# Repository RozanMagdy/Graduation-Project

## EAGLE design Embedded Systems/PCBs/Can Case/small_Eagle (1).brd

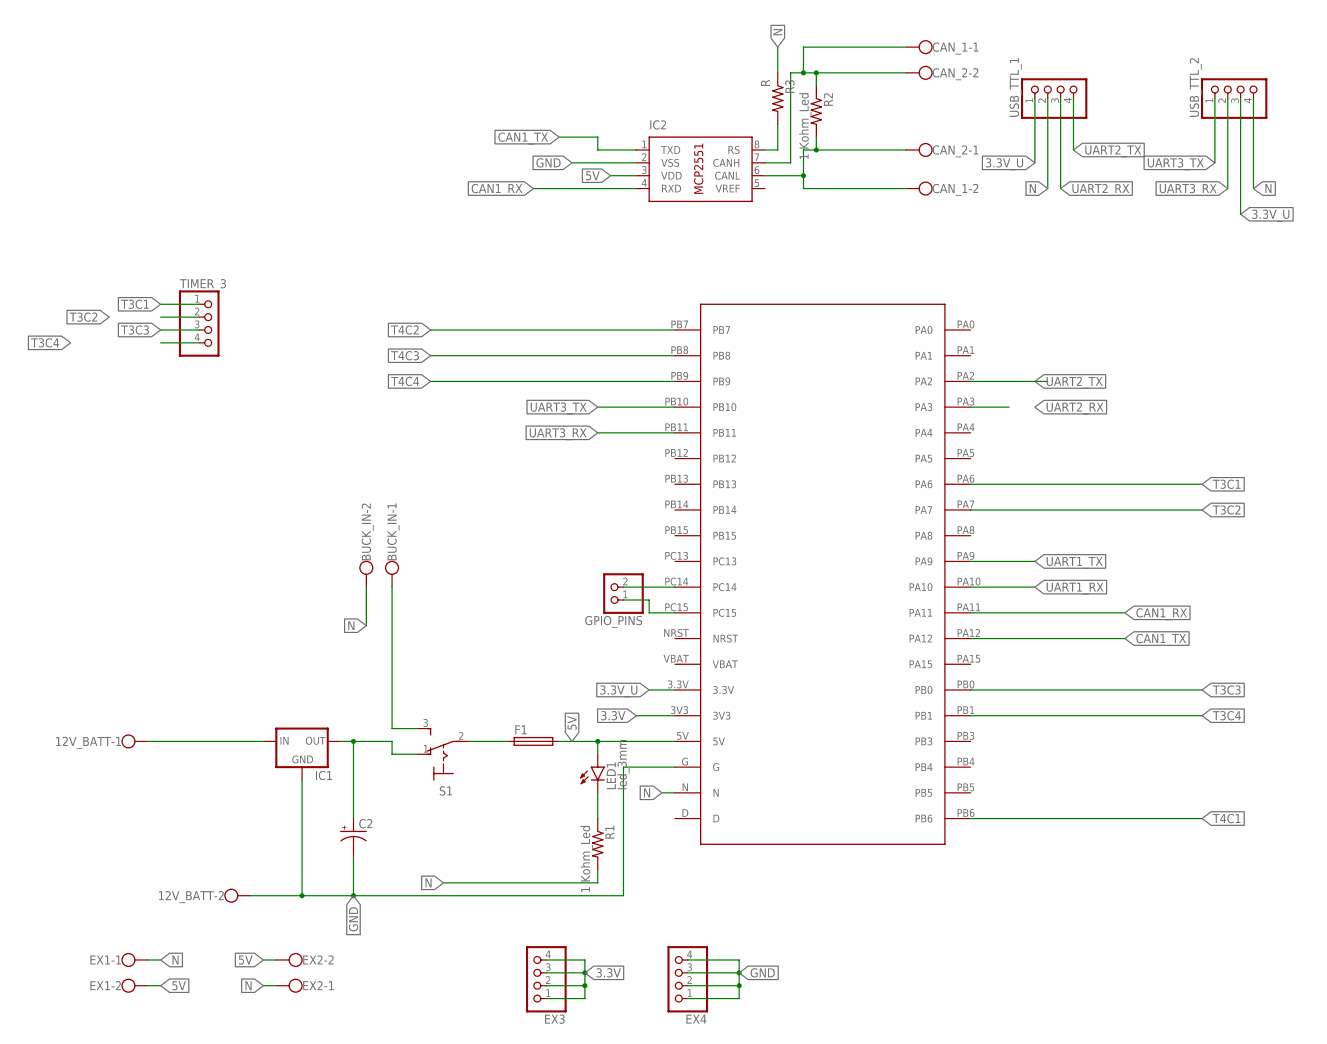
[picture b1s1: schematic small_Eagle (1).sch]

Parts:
12V_BATT: W237-102
BUCK_IN: W237-102
C2: CPOL-USE2-4; E2-4
CAN_1, CAN_2: W237-102
EX1, EX2: W237-102
EX3, EX4: PINHD-1X4; 1X04
F1: GSH15
GPIO_PINS: PINHD-1X2; 1X02
IC1: 78XXS
IC2: MCP2551/P; DIL08
LED1: led_3mm; LED3MM
R1, R2: 1 Kohm_Led; 0207/7
R3: R; 0207/7
S1: 320-916
TIMER_3: PINHD-1X4; 1X04
U$1: STM32F103C8; DIP
USB_TTL_1, USB_TTL_2: PINHD-1X4; 1X04

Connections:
3.3V: EX3.1, EX3.2, EX3.3, EX3.4, U$1.3V3
3.3V_U: U$1.3.3V, USB_TTL_1.1, USB_TTL_2.3
5V: EX1.2, EX2.2, F1.2, IC2.3 (VDD), LED1.A, U$1.5V
CAN1_RX: IC2.4 (RXD), U$1.PA11
CAN1_TX: IC2.1 (TXD), U$1.PA12
GND: 12V_BATT.2, C2.-, EX4.1, EX4.2, EX4.3, EX4.4, IC1.GND, IC2.2 (VSS), U$1.G
GPIO_PINS: GPIO_PINS.1, U$1.PC15
N: BUCK_IN.2, EX1.1, EX2.1, R1.2, R3.1, U$1.N, USB_TTL_1.2, USB_TTL_2.4
unnamed: BUCK_IN.1, S1.3 (S)
unnamed: CAN_1.2, CAN_2.1, IC2.6 (CANL), R2.2
unnamed: LED1.K (C), R1.1
unnamed: F1.1, S1.2
unnamed: 12V_BATT.1, IC1.IN
unnamed: C2.+, IC1.OUT, S1.1 (O)
unnamed: IC2.8 (RS), R3.2
unnamed: GPIO_PINS.2, U$1.PC14
unnamed: CAN_1.1, CAN_2.2, IC2.7 (CANH), R2.1
T3C1: TIMER_3.1, U$1.PA6
T3C2: TIMER_3.2, U$1.PA7
T3C3: TIMER_3.3, U$1.PB0
T3C4: TIMER_3.4, U$1.PB1
T4C1: U$1.PB6
T4C2: U$1.PB7
T4C3: U$1.PB8
T4C4: U$1.PB9
UART1_RX: U$1.PA10
UART1_TX: U$1.PA9
UART2_RX: U$1.PA3, USB_TTL_1.3
UART2_TX: U$1.PA2, USB_TTL_1.4
UART3_RX: U$1.PB11, USB_TTL_2.2
UART3_TX: U$1.PB10, USB_TTL_2.1

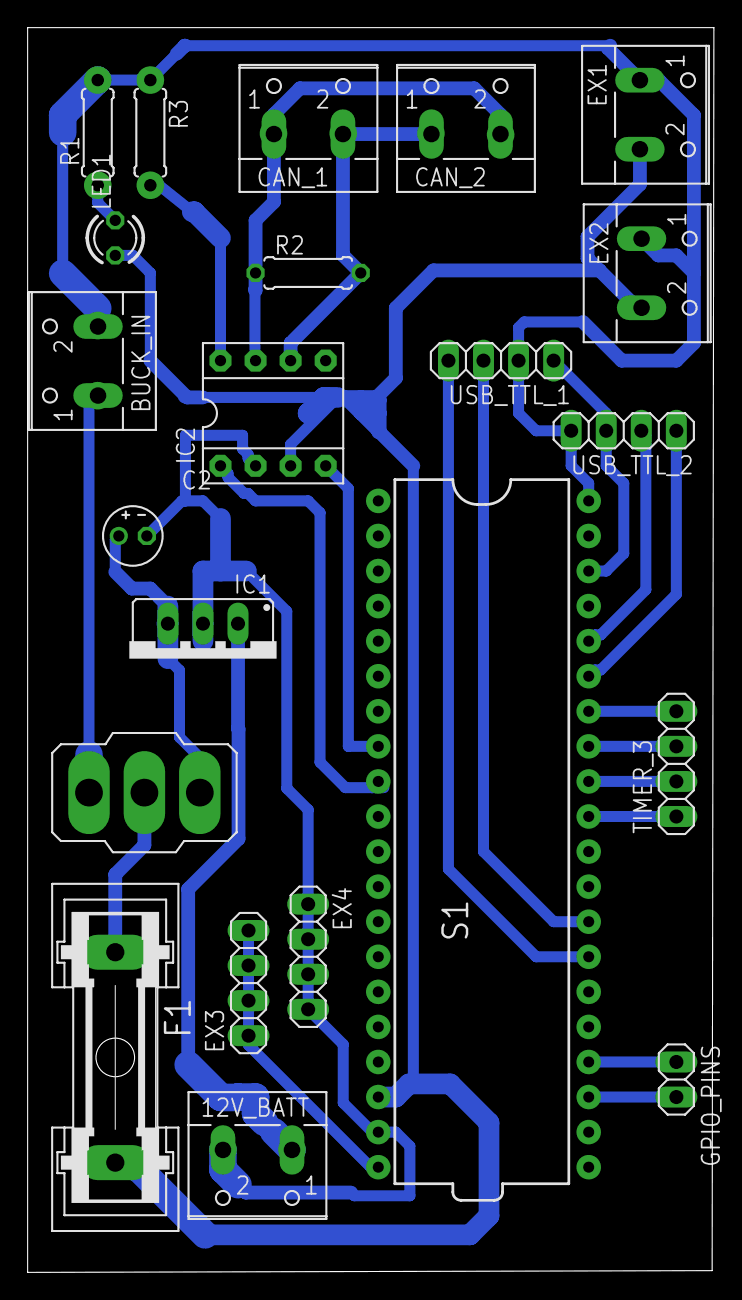
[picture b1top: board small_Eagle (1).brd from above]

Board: 2 copper layers, 49.7 x 90.2 mm, 22 parts (0 on the bottom side), 25 nets.

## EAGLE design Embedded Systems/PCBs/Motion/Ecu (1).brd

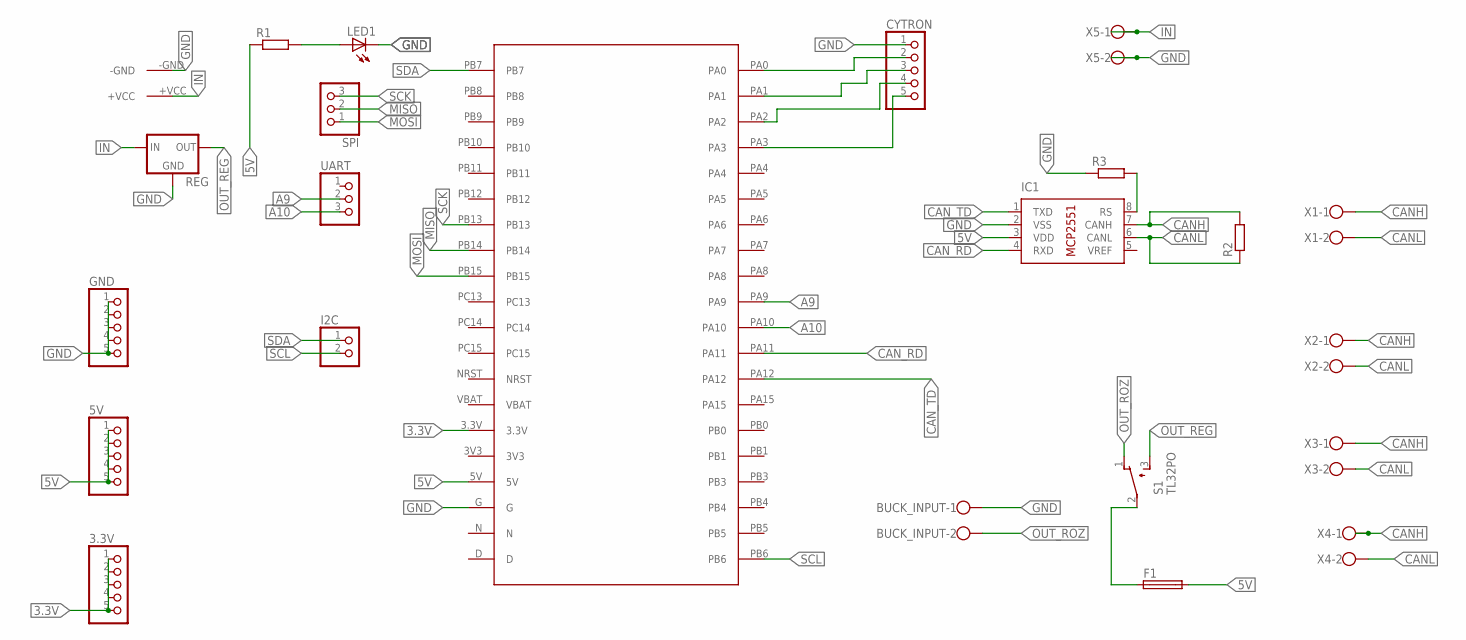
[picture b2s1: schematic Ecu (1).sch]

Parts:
3.3V, 5V: PINHD-1X5; 1X05
BUCK_INPUT: W237-102
CYTRON: PINHD-1X5; 1X05
F1: GSH15
GND: PINHD-1X5; 1X05
I2C: PINHD-1X2; 1X02
IC1: MCP2551/P; DIL08
LED1: LED5MM
MM1: XT60
R1, R2, R3: R-EU_0207/10; 0207/10
REG: 78XXS
S1: TL32PO; TL3XPO
SPI: PINHD-1X3; 1X03
U$3: STM32F103C8; DIP
UART: PINHD-1X3; 1X03
X1, X2, X3, X4, X5: W237-102

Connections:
3.3V: 3.3V.1, 3.3V.5, U$3.3.3V
5V: 5V.1, 5V.5, F1.2, IC1.3 (VDD), R1.1, U$3.5V
A9: U$3.PA9, UART.2
A10: U$3.PA10, UART.3
CANH: IC1.7 (CANH), R2.2, X1.1, X2.1, X3.1, X4.1
CANL: IC1.6 (CANL), R2.1, X1.2, X2.2, X3.2, X4.2
CAN_RD: IC1.4 (RXD), U$3.PA11
CAN_TD: IC1.1 (TXD), U$3.PA12
GND: BUCK_INPUT.1, CYTRON.1, GND.1, GND.5, IC1.2 (VSS), LED1.K (C), MM1.-GND, R3.1, REG.GND, U$3.G, X5.2
IN: MM1.+VCC, REG.IN, X5.1
MISO: SPI.2, U$3.PB14
MOSI: SPI.1, U$3.PB15
unnamed: LED1.A, R1.2
unnamed: CYTRON.2, U$3.PA0
unnamed: CYTRON.4, U$3.PA2
unnamed: CYTRON.3, U$3.PA1
unnamed: CYTRON.5, U$3.PA3
unnamed: IC1.8 (RS), R3.2
unnamed: F1.1, S1.2
OUT_REG: REG.OUT, S1.3 (S)
OUT_ROZ: BUCK_INPUT.2, S1.1 (O)
SCK: SPI.3, U$3.PB13
SCL: I2C.2, U$3.PB6
SDA: I2C.1, U$3.PB7

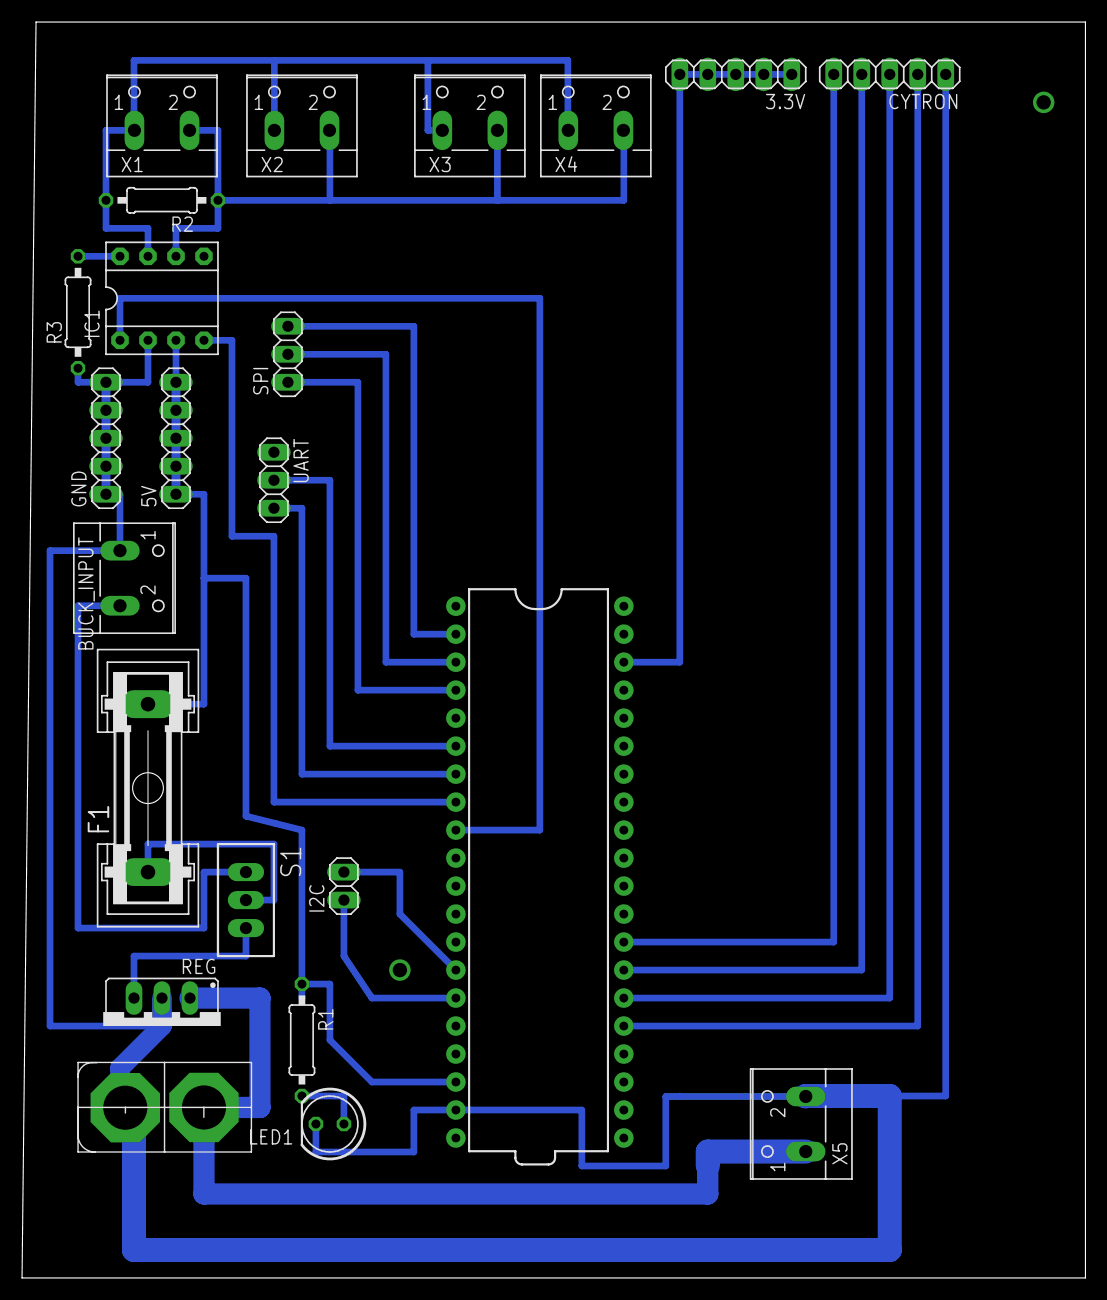
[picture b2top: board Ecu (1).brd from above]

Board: 2 copper layers, 96.5 x 114.0 mm, 23 parts (0 on the bottom side), 24 nets.

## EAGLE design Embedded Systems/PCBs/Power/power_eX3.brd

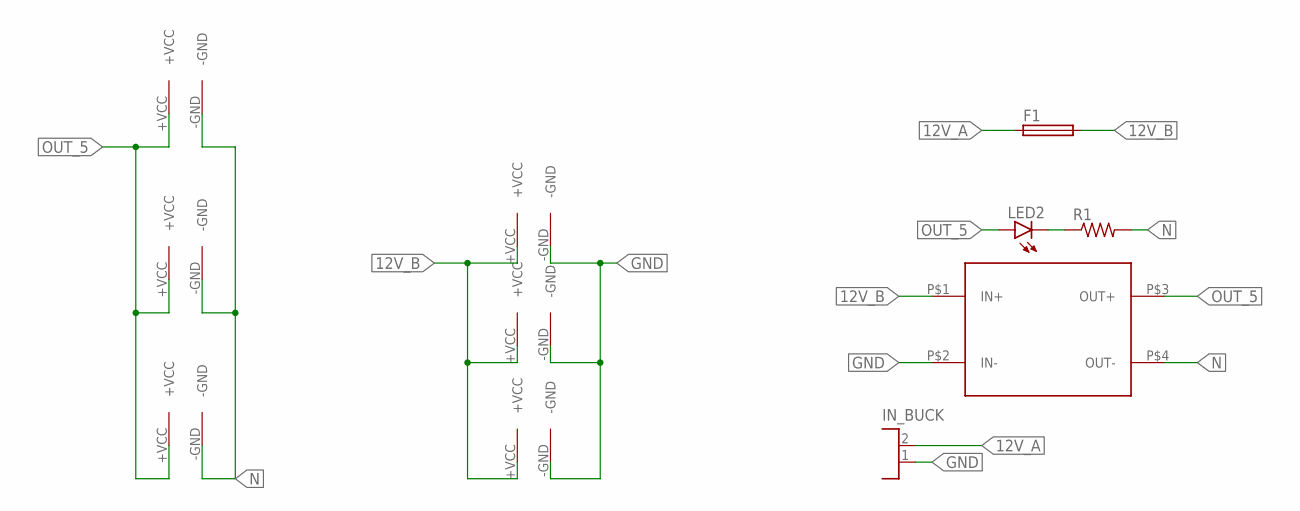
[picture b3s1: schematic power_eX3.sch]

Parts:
F1: GSH15
IN_BUCK: 2P; DG55CB-2P-1
LED2: LED3MM
MM1, MM2, MM3, MM4, MM5, MM6: XT60
R1: R-US_0207/7; 0207/7
U$2: LM2595_BUCK_5A_LEDDIP8; LM2595_BUCK_5A_LED

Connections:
12V_A: F1.1, IN_BUCK.2
12V_B: F1.2, MM4.+VCC, MM5.+VCC, MM6.+VCC, U$2.P$1 (IN+)
GND: IN_BUCK.1, MM4.-GND, MM5.-GND, MM6.-GND, U$2.P$2 (IN-)
N: MM1.-GND, MM2.-GND, MM3.-GND, R1.2, U$2.P$4 (OUT-)
unnamed: LED2.K (C), R1.1
OUT_5: LED2.A, MM1.+VCC, MM2.+VCC, MM3.+VCC, U$2.P$3 (OUT+)

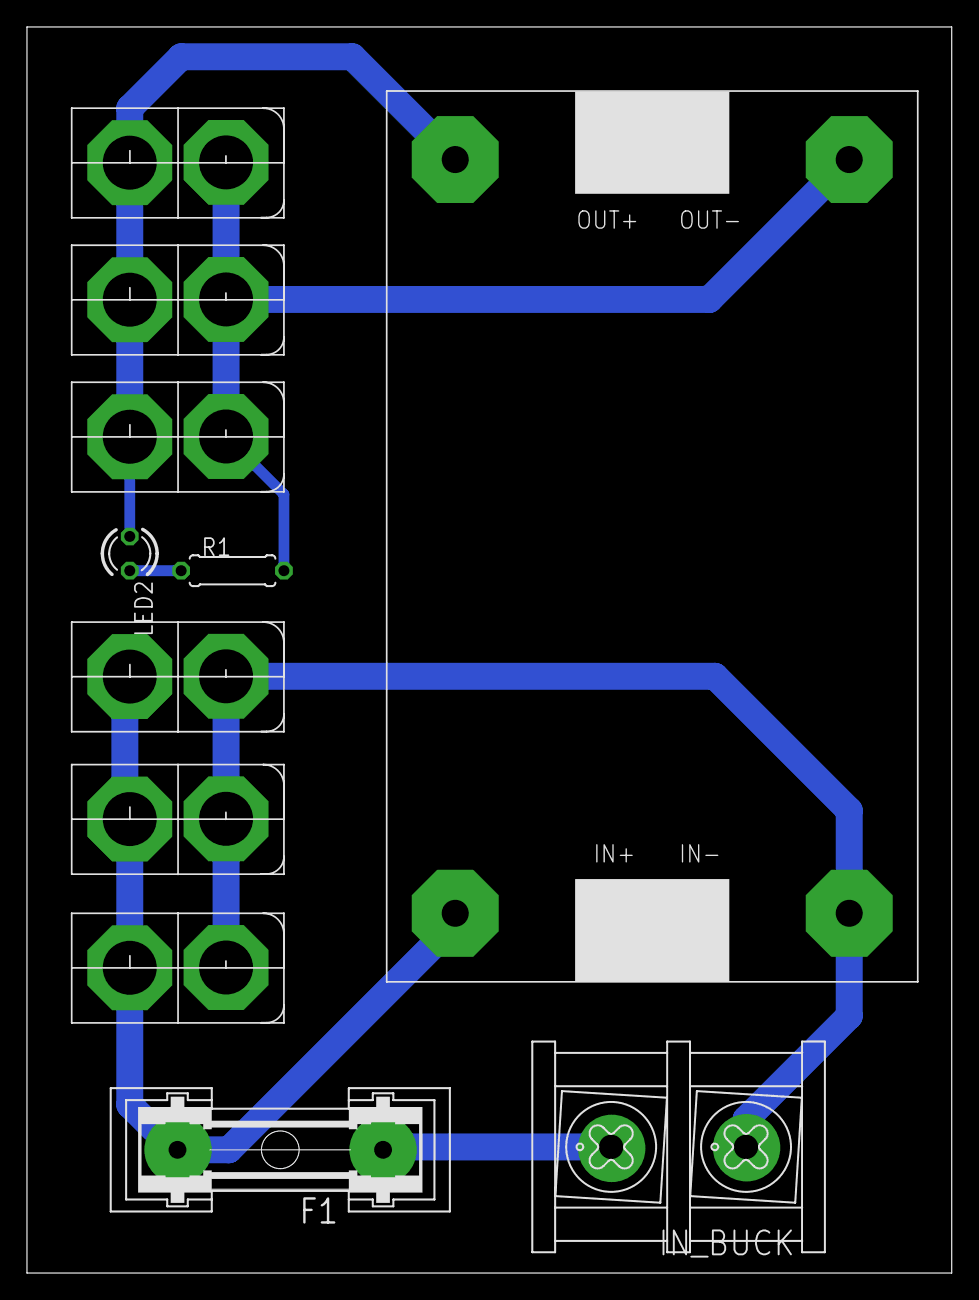
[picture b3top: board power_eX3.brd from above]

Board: 2 copper layers, 68.6 x 92.4 mm, 11 parts (0 on the bottom side), 6 nets.

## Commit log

2021-05-24 added GP files
